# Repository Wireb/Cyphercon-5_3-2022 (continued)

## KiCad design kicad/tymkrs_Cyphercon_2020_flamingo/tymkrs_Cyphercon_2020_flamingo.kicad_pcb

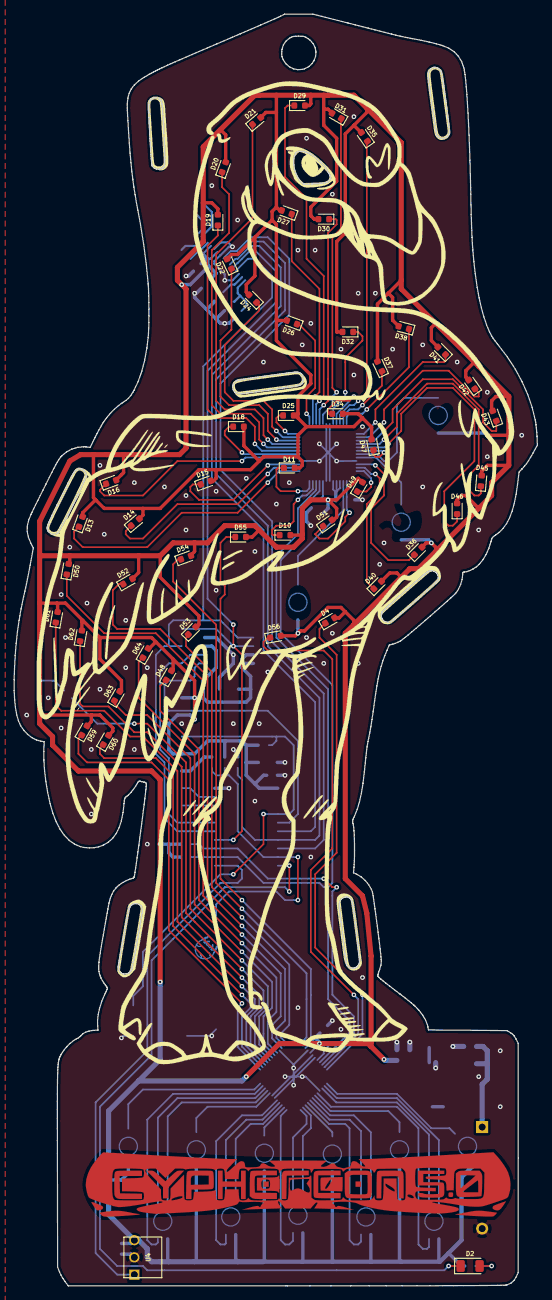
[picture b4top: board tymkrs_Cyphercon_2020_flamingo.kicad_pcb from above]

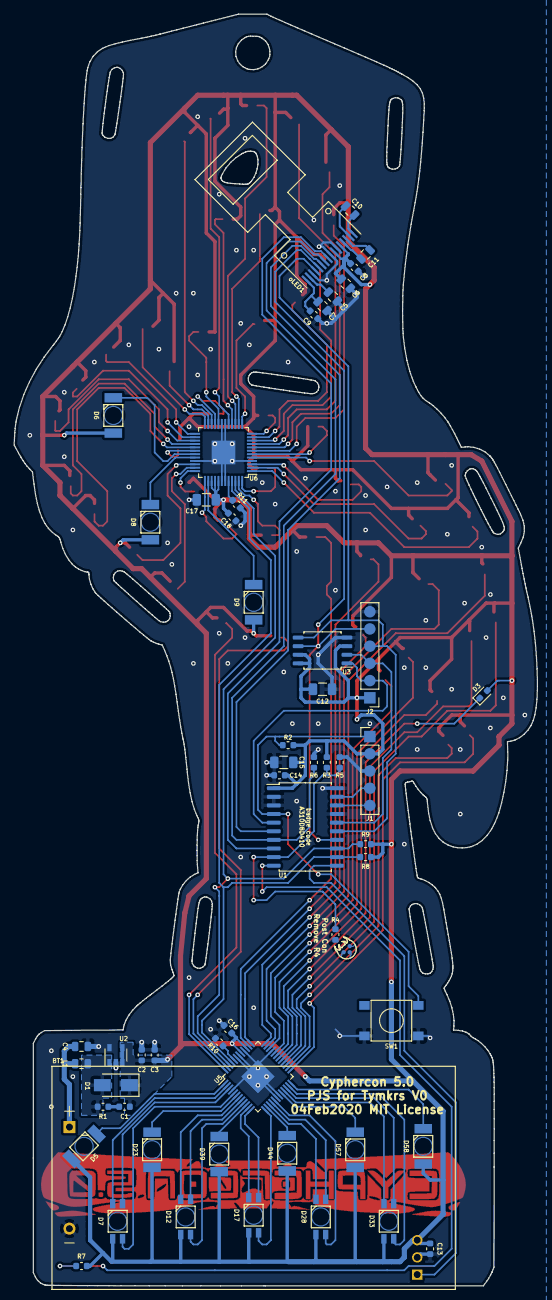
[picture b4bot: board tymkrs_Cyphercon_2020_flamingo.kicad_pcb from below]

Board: 2 copper layers, 77.2 x 187.6 mm, 114 parts (57 on the bottom side), 101 nets.

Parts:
BT1: Keystone 2462; Keystone_2462_2x_AA_no_holes
C1: no_pop; C_0603_1608Metric
C2, C3: 22uF 10V; C_0603_1608Metric
C4, C6, C7: 4.7uF 16V 0805; C_0805_2012Metric
C5: 2.2uF 16V 0805; C_0805_2012Metric
C8: 0.1uF 6.3V X5R; C_0603_1608Metric
C9: 0.1uF 16V X7R; C_0603_1608Metric
C10, C11: 1uF 16V; C_0805_2012Metric
C12, C15, C17: 10uF; C_1206_3216Metric
C13, C14, C16, C18: 0.1uF; C_0603_1608Metric
D1: no-pop; D_SMA
D2: IR26-21C (1206); LED_1206_3216Metric
D3: White IN-S63AT5UW; LED_0603_1608Metric
D4, D10, D11, D13, D14, D15, D16, D18, D19, D20, D21, D22, D24, D25, D26, D27, D29, D30, D31, D32, D34, D35, D36, D37, D38, D40, D41, D42, D43, D45, D46, D47, D48, D49, D50, D51, D52, D53, D54, D55, D56, D59, D60, D61, D62, D63, D64: Pink_0603; LED_0603_1608Metric
D5, D23, D39, D44, D57, D58: Amber; XZ__K45WT-9
D6, D8, D9: Red_rev; XZ__K45WT-9
D7, D12, D17, D28, D33: LED_RABG; XZMDKCBDDG45S-9
J1: PicKit; PinHeader_1x05_P2.54mm_Vertical
J2: SPI; PinHeader_1x06_P2.54mm_Vertical
L1: 2.2uH 1.6A 0805; L_0805_2012Metric
R1, R5: no_pop; R_0603_1608Metric
R2, R3, R6: 100k; R_0603_1608Metric
R4: 1k; R_0603_1608Metric
R7: 27 (0805); R_0603_1608Metric
R8, R9: 10k; R_0603_1608Metric
R10, R11: 24.9K; R_0603_1608Metric
SW1: TACT_6MM; PTS645_6mm_tact_sw
U1: PIC16F15345; SOIC-20W_7.5x12.8mm_P1.27mm
U2: TPS61322x; SOT-23-5
U3: 25LCxxx; SOIC-8_5.275x5.275mm_P1.27mm
U4: TSOP58438; TSOP48
U5, U6: IS31FL3236_TQFP; TQFP-48-1EP_7x7mm_P0.5mm_EP3.5x3.5mm
icon1: Metroid; metroid
icon2: Common Logo soldermask; cypheron2020_common_logo_soldermask
icon3: Common LED guide; cypheron2020_common_logo_led_guide
icon5: Common Logo copper; cypheron2020_common_logo_copper_add
icon6: Cut lines; cypheron2020_flamingo_cuts
icon8: Icon soldermask; cypheron2020_flamingo_icons_soldermask
icon9: LED guide; cypheron2020_flamingo_led_guide
icon10: Silk; cypheron2020_flamingo_silk
icon11: Eye location; cypheron2020_flamingo_eye
oLED1: 0.42_oLED_display; oLED_0.42_rev

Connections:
+3V3: C1.1, C2.1, C3.1, C6.1, C8.1, C12.1, C13.1, C14.1, C15.1, C16.1, C17.1, C18.1, D1.1, D3.2, D4.2, D5.2, D6.2, D7.2, D8.2, D9.2, D10.2, D11.2, D12.2, D13.2, D14.2, D15.2, D16.2, D17.2, D18.2, D19.2, D20.2, D21.2, D22.2, D23.2, D24.2, D25.2, D26.2, D27.2, D28.2, D29.2, D30.2, D31.2, D32.2, D33.2, D34.2, D35.2, D36.2, D37.2, D38.2, D39.2, D40.2, D41.2, D42.2, D43.2, D44.2, D45.2, D46.2, D47.2, D48.2, D49.2, D50.2, D51.2, D52.2, D53.2, D54.2, D55.2, D56.2, D57.2, D58.2, D59.2, D60.2, D61.2, D62.2, D63.2, D64.2, J1.2, J2.1, R2.1, R3.1, R7.2, R8.2, R9.2, U1.1, U2.3, U2.4, U3.3, U3.7, U3.8, U4.3, U5.39, U5.41, U6.39, U6.40, U6.41, oLED1.5, oLED1.7
EEPROM_CS: J2.2, U1.5, U3.1
GND: BT1.2, C2.2, C3.2, C4.2, C5.1, C6.2, C7.1, C8.2, C9.1, C12.2, C13.2, C14.2, C15.2, C16.2, C17.2, C18.2, J1.3, J2.6, R4.2, R5.2, R6.2, R10.1, R11.1, SW1.3, SW1.4, U1.2, U1.3, U1.17, U1.20, U2.2, U2.5, U3.4, U4.2, U5.4, U5.18, U5.19, U5.33, U5.40, U5.42, U5.43, U5.49, U6.4, U6.18, U6.19, U6.33, U6.42, U6.43, U6.49, oLED1.6, oLED1.8, oLED1.14
IR_IN: U1.11, U4.1
IR_OUT: D2.1, U1.10
MISO: J2.3, U1.16, U3.2
MOSI: J2.4, U1.15, U3.5, oLED1.13
unnamed: BT1.1, C4.1, L1.1
unnamed: C1.2, R1.1
unnamed: C5.2, oLED1.15
unnamed: C7.2, C9.2, oLED1.16
unnamed: C10.1, oLED1.1
unnamed: C10.2, oLED1.2
unnamed: C11.1, oLED1.3
unnamed: C11.2, oLED1.4
unnamed: D1.2, L1.2, R1.2, U2.1
unnamed: D2.2, R7.1
unnamed: D3.1, U5.29
unnamed: D4.1, U5.48
unnamed: D5.1, U5.1
unnamed: D6.1, U6.31
unnamed: D7.1, U5.2
unnamed: D7.3, U5.5
unnamed: D7.4, U5.3
unnamed: D8.1, U6.32
unnamed: D9.1, U6.38
unnamed: D10.1, U6.47
unnamed: D11.1, U6.48
unnamed: D12.1, U5.7
unnamed: D12.3, U5.9
unnamed: D12.4, U5.8
unnamed: D13.1, U6.1
unnamed: D14.1, U6.2
unnamed: D15.1, U6.3
unnamed: D16.1, U6.5
unnamed: D17.1, U5.11
unnamed: D17.3, U5.13
unnamed: D17.4, U5.12
unnamed: D18.1, U6.6
unnamed: D19.1, U6.7
unnamed: D20.1, U6.8
unnamed: D21.1, U6.9
unnamed: D22.1, U6.10
unnamed: D23.1, U5.6
unnamed: D24.1, U6.11
unnamed: D25.1, U6.12
unnamed: D26.1, U6.13
unnamed: D27.1, U6.14
unnamed: D28.1, U5.15
unnamed: D28.3, U5.17
unnamed: D28.4, U5.16
unnamed: D29.1, U6.15
unnamed: D30.1, U6.16
unnamed: D31.1, U6.17
unnamed: D32.1, U6.20
unnamed: D33.1, U5.21
unnamed: D33.3, U5.23
unnamed: D33.4, U5.22
unnamed: D34.1, U6.21
unnamed: D35.1, U6.22
unnamed: D36.1, U6.34
unnamed: D37.1, U6.23
unnamed: D38.1, U6.24
unnamed: D39.1, U5.10
unnamed: D40.1, U6.35
unnamed: D41.1, U6.25
unnamed: D42.1, U6.26
unnamed: D43.1, U6.27
unnamed: D44.1, U5.14
unnamed: D45.1, U6.28
unnamed: D46.1, U6.29
unnamed: D47.1, U6.30
unnamed: D48.1, U5.32
unnamed: D49.1, U6.36
unnamed: D50.1, U5.34
unnamed: D51.1, U6.37
unnamed: D52.1, U5.35
unnamed: D53.1, U5.36
unnamed: D54.1, U5.37
unnamed: D55.1, U5.38
unnamed: D56.1, U5.47
unnamed: D57.1, U5.20
unnamed: D58.1, U5.24
unnamed: D59.1, U5.25
unnamed: D60.1, U5.26
unnamed: D61.1, U5.27
unnamed: D62.1, U5.28
unnamed: D63.1, U5.30
unnamed: D64.1, U5.31
unnamed: J1.1, R2.2, SW1.2, U1.4
unnamed: J1.4, U1.19
unnamed: J1.5, U1.18
unnamed: R10.2, U5.44
unnamed: R11.2, U6.44
POST_CON: R3.2, R4.1, R5.1, U1.9
SCL: R9.1, U1.13, U5.46, U6.46
SDA: R8.1, U1.12, U5.45, U6.45
Sclk: J2.5, U1.14, U3.6, oLED1.12
oLED_CS: U1.8, oLED1.9
oLED_DC: U1.6, oLED1.11
oLED_Reset: R6.1, U1.7, oLED1.10

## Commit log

2022-05-03 First push
    I think this includes all the files I have related to cyphercon 5.3 badges and support hardware.
